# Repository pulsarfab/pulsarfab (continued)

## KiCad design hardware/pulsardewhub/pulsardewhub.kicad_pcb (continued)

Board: 4 copper layers, 233 parts (0 on the bottom side), 133 nets, no tracks yet.

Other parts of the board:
FID1, FID2, FID3: Fiducial; Fiducial_1mm_Mask2mm
H1, H2, H3, H4: M3; MountingHole_3.2mm_M3

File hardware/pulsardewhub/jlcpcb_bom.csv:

"Item","Designator","Comment","Footprint","Qty","LCSC Part #","MPN","Manufacturer"
"1","C1,C3,C4,C23,C33,C50,C52,C70,C71,C501,C503,C601,C603,C701,C703,C801,C803,C903-C909,C914,C915","100n","Capacitor_SMD:C_0603_1608Metric","26","C14663","CC0603KRX7R9BB104","YAGEO"
"2","C2","4.7u / 16V","Capacitor_SMD:C_0603_1608Metric","1","C19666","CL10A475KO8NNNC","Samsung Electro-Mechanics"
"3","C10,C22,C51,C910-C913","1u / 50V","Capacitor_SMD:C_0603_1608Metric","7","C15849","CL10A105KB8NNNC","Samsung Electro-Mechanics"
"4","C11,C13,C31,C101,C102,C201,C202,C301,C302,C401,C402","100n / 50V","Capacitor_SMD:C_0603_1608Metric","11","C14663","CC0603KRX7R9BB104","YAGEO"
"5","C12","470u / 35V","Capacitor_THT:CP_Radial_D10.0mm_P5.00mm","1","C106703","ERS1VM471G16OT","AISHI"
"6","C20,C30","10u / 50V","Capacitor_SMD:C_1210_3225Metric","2","C138687","CL32B106KBJNNNE","Samsung Electro-Mechanics"
"7","C21","220n / 50V","Capacitor_SMD:C_0603_1608Metric","1","C64705","CL10B224KB8NNNC","Samsung Electro-Mechanics"
"8","C24-C27,C34-C37","22u / 25V","Capacitor_SMD:C_1206_3216Metric","8","C12891","CL31A226KAHNNNE","Samsung Electro-Mechanics"
"9","C103,C203,C303,C403","4.7n / 50V","Capacitor_SMD:C_0603_1608Metric","4","C1621","CL10B472KB8NNNC","Samsung Electro-Mechanics"
"10","C104,C204,C304,C404","10n","Capacitor_SMD:C_0603_1608Metric","4","C1589","CL10B103KB8NNNC","Samsung Electro-Mechanics"
"11","C502,C602,C702,C802","150u / 10V / 20%","pulsarfab:CP_RVT_D6.3mm_L5.4mm","4","C970688","RVT1A151M0605 150UF 10V","DMBJ"
"12","C901,C902","18p / C0G","Capacitor_SMD:C_0603_1608Metric","2","C342890","CGA3E2C0G1H180JT0Y0N","TDK"
"13","D10","SMCJ18A","Diode_SMD:D_SMC","1","C438102","SMCJ18A","Jingdao Microelectronics"
"14","D51,D61","SMBJ20A","Diode_SMD:D_SMB","2","C364296","SMBJ20A","MDD(Microdiode Semiconductor)"
"15","D101,D201,D301,D401","SS54","Diode_SMD:D_SMA","4","C22452","SS54","MDD(Microdiode Semiconductor)"
"16","F10","30A / upstream budget","pulsarfab:Fuse_S1032_10.3x3.2mm","1","C553917","S1032-F-30.0A","SART"
"17","F51,F61","7A heater fuse","Fuse:Fuse_Littelfuse-NANO2-451_453","2","C99548","0451007.MRL","Littelfuse"
"18","J1","SWD","Connector_PinHeader_2.54mm:PinHeader_1x05_P2.54mm_Vertical","1","C492404","PZ254V-11-05P","XFCN"
"19","J10","XT60: 2=PLUS, 1=GND","pulsarfab:AMASS_XT60PW-M_Edge","1","C98732","XT60PW-M","Changzhou Amass Elec"
"20","J40","USB-C upstream","pulsarfab:USB_C_HRO_TYPE-C-31-M-12","1","C165948","TYPE-C-31-M-12","Korean Hroparts Elec"
"21","J51","HEATER 1","pulsarfab:TerminalBlock_KEFA_KF128_2P_P5.08mm","1","C474952","KF128-5.08-2P-AA","Cixi Kefa Elec"
"22","J61","HEATER 2","pulsarfab:TerminalBlock_KEFA_KF128_2P_P5.08mm","1","C474952","KF128-5.08-2P-AA","Cixi Kefa Elec"
"23","J101,J201,J301,J401","5A DC / center +","pulsarfab:BarrelJack_XKB_DC-005K-5A_Edge","4","C2880546","DC-005K-5A-2.0","XKB Connection"
"24","J501,J601,J701,J801","USB-A / 500mA","pulsarfab:USB_A_SHOUHAN_AF90ZJWG_THT","4","C456019","AF 90 ZJWG","SHOU HAN"
"25","L20","8.2u / 10A sat","pulsarfab:L_SXN_SMMS1050","1","C149543","SMMS1050-8R2M","Shun Xiang Nuo"
"26","L30","6.8u / 12A sat","pulsarfab:L_SXN_SMMS1050","1","C149542","SMMS1050-6R8M","Shun Xiang Nuo"
"27","Q10,Q11","SiR680LDP","Package_SO:PowerPAK_SO-8_Single","2","C3279524","SIR680LDP-T1-RE3","Vishay"
"28","Q51,Q61","AOD4184A","Package_TO_SOT_SMD:TO-252-2","2","C5370959","AOD4184A","TECH PUBLIC"
"29","R1,R2","4.7k","Resistor_SMD:R_0603_1608Metric","2","C23162","0603WAF4701T5E","UNI-ROYAL"
"30","R20,R30,R53,R63,R101,R201,R301,R401,R502,R602,R702,R802,R923,R924","100k","Resistor_SMD:R_0603_1608Metric","14","C25803","0603WAF1003T5E","UNI-ROYAL"
"31","R21","24.9k","Resistor_SMD:R_0603_1608Metric","1","C25962","0603WAF2492T5E","UNI-ROYAL"
"32","R31,R102,R202,R302,R402","20k","Resistor_SMD:R_0603_1608Metric","5","C4184","0603WAF2002T5E","UNI-ROYAL"
"33","R32","12k","Resistor_SMD:R_0603_1608Metric","1","C22790","0603WAF1202T5E","UNI-ROYAL"
"34","R50","2m / 3W / 1%","Resistor_SMD:R_2512_6332Metric","1","C2994640","HoLLR2512-3W-2mR-1%","Milliohm"
"35","R51,R61,R71,R73-R78,R104-R106,R109,R204-R206,R209,R304-R306,R309,R404-R406,R409,R901-R918,R920,R925-R928","10k","Resistor_SMD:R_0603_1608Metric","48","C25804","0603WAF1002T5E","UNI-ROYAL"
"36","R52,R62","47","Resistor_SMD:R_0603_1608Metric","2","C23182","0603WAF470JT5E","UNI-ROYAL"
"37","R70","220k","Resistor_SMD:R_0603_1608Metric","1","C22961","0603WAF2203T5E","UNI-ROYAL"
"38","R72","470k","Resistor_SMD:R_0603_1608Metric","1","C23178","0603WAF4703T5E","UNI-ROYAL"
"39","R103,R203,R303,R403","150k","Resistor_SMD:R_0603_1608Metric","4","C22807","0603WAF1503T5E","UNI-ROYAL"
"40","R107,R207,R307,R407","1k / 1%","Resistor_SMD:R_0603_1608Metric","4","C21190","0603WAF1001T5E","UNI-ROYAL"
"41","R110,R210,R310,R410","1k","Resistor_SMD:R_0603_1608Metric","4","C21190","0603WAF1001T5E","UNI-ROYAL"
"42","R501,R601,R701,R801","43.2k / 1%","Resistor_SMD:R_0603_1608Metric","4","C23053","0603WAF4322T5E","UNI-ROYAL"
"43","R919","12k / 1%","Resistor_SMD:R_0603_1608Metric","1","C22790","0603WAF1202T5E","UNI-ROYAL"
"44","R921,R922","5.1k","Resistor_SMD:R_0603_1608Metric","2","C23186","0603WAF5101T5E","UNI-ROYAL"
"45","U1","STM32G0B1KBU6","Package_DFN_QFN:UFQFPN-32-1EP_5x5mm_P0.5mm_EP3.5x3.5mm","1","C5159549","STM32G0B1KBU6","ST"
"46","U2","SHT40-AD1B-R2","Sensor_Humidity:Sensirion_DFN-4_1.5x1.5mm_P0.8mm_SHT4x_NoCentralPad","1","C2909890","SHT40-AD1B-R2","Sensirion"
"47","U10","LM74700QDBV","Package_TO_SOT_SMD:SOT-23-6","1","C2941042","LM74700QDBVRQ1","TI"
"48","U20","LMR33630ADDA","Package_SO:Texas_HSOP-8-1EP_3.9x4.9mm_P1.27mm","1","C841384","LMR33630ADDAR","TI"
"49","U30","LMR51610XDBVR","Package_TO_SOT_SMD:SOT-23-6","1","C20539658","LMR51610XDBVR","Texas Instruments"
"50","U40","USB2517-JZX","Package_DFN_QFN:QFN-64-1EP_9x9mm_P0.5mm_EP4.7x4.7mm","1","C1521556","USB2517-JZX","MICROCHIP"
"51","U41","TPS3808G33DBV","Package_TO_SOT_SMD:SOT-23-6","1","C43698","TPS3808G33DBVR","TI"
"52","U42,U502,U602,U702,U802","USBLC6-2SC6","Package_TO_SOT_SMD:SOT-23-6","5","C7519","USBLC6-2SC6","ST"
"53","U50","TC4427AVOA713","Package_SO:SOIC-8_3.9x4.9mm_P1.27mm","1","C624944","TC4427AVOA713","MICROCHIP"
"54","U51","INA226","Package_SO:TSSOP-10_3x3mm_P0.5mm","1","C49851","INA226AIDGSR","Texas Instruments"
"55","U70","TPS3700DDC","Package_TO_SOT_SMD:SOT-23-6","1","C33002","TPS3700DDCR","TI"
"56","U71","SN74LVC08APW","Package_SO:TSSOP-14_4.4x5mm_P0.65mm","1","C465737","SN74LVC08APWR","Texas Instruments"
"57","U101,U201,U301,U401","TPS25974LRPW","pulsarfab:TI_RPW0010A_VQFN10_2x2mm","4","C3662931","TPS25974LRPWR","Texas Instruments"
"58","U102,U202,U302,U402","TVS1800DRV","Package_SON:WSON-6-1EP_2x2mm_P0.65mm_EP1x1.6mm","4","C2649846","TVS1800DRVR","Texas Instruments"
"59","U501,U601,U701,U801","TPS2553DBV","Package_TO_SOT_SMD:SOT-23-6","4","C55266","TPS2553DBVR","TI"
"60","Y40","24MHz / CL=12pF","Crystal:Crystal_SMD_3225-4Pin_3.2x2.5mm","1","C5181479","3225 24M 12PF 10PPM","SOSET"

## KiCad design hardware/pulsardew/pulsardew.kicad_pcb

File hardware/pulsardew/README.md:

# PulsarDew schematic

PulsarDew is the original four-channel dew heater controller. For the expanded
product with switched DC power outlets, two heaters and a USB hub, see
**[PulsarPower](../pulsardewhub/README.md)** (formerly PulsarDew Hub).

Open `pulsardew.kicad_pro` in KiCad 10, then open its root schematic. Revision
0.2 is a connected nine-page hierarchy: system wiring, controller, current
monitor, logic supply, SHT40, and four instances of the heater driver.
Edit the `.kicad_sch` files directly in KiCad; they are the authoritative design.

## Electrical connections

The root drawing shows the protected DC supply through the 2 mΩ shunt to all
four heaters. The logic regulator branches off before the shunt. The INA226
therefore measures **combined heater current**, including gate-drive current,
not four independent currents. Its address is 0x40; the SHT40 address is 0x44.

| Signal | MCU pin | Connection |
| --- | --- | --- |
| Heater 0–3 PWM | PA0–PA3, pads 7–10 | Four independent driver inputs; active low |
| I2C SCL / SDA | PB6 / PB7, pads 30 / 31 | INA226 and SHT40, one pair of 4.7 kΩ pull-ups |
| USB D− / D+ | PA11 / PA12, pads 22 / 23 | Both corresponding USB-C pin pairs |
| USB VBUS sense | PA9, pad 19 | 100 kΩ / 100 kΩ divider |
| SWDIO / SWCLK | PA13 / PA14, pads 24 / 25 | J4 pins 2 / 3 |
| Reset | PF2/NRST, pad 6 | 100 nF to ground and J4 pin 4 |

J4 pins 1 and 5 provide target voltage reference and ground. J101, J201, J301,
and J401 are heater connectors: pin 1 is measured VIN; pin 2 is a switched
return and must not be connected directly to ground. J2 and J3 are parallel
power-input options; use one supply source.

USB is self-powered from the DC supply. USB VBUS is only sensed and is isolated
from the DC and 3.3 V rails. Firmware must disable the MCU's UCPD dead-battery
pull-down on PA9 before sensing VBUS and must enable USB attachment only while
VBUS is present. Firmware implementation is outside this schematic change.

## Repairs made in revision 0.2

- Restored qualified symbol caches and per-sheet instance references. The
  previous files loaded as missing symbols and exported no components.
- Rewired the hierarchy and component pins, with visible branches and junctions.
- Corrected the 2N7002 to gate/source/drain pads 1/2/3. The AOD4184A uses
  gate/drain/source pads 1/2/3.
- Corrected I2C to PB6/PB7; completed both USB-C orientations, reset, bypass
  capacitors, debug access, power input and heater outputs.
- Replaced the incorrectly substituted L78L33 symbol and 12 V HT7333-A part
  with a dedicated **HT7333-1** symbol: pad 1 GND, pad 2 VIN/tab, pad 3 VOUT.
  This retains the stated 12–20 V input range. Input/output bypassing is
  10 µF plus 100 nF as shown in the manufacturer's application circuit.
- Corrected resistor footprint assignments and the missing terminal-block
  library reference. New or changed components without confirmed sourcing
  have no invented LCSC number.

## Reproducible verification

From `hardware/`:

```sh
make check-pulsardew
make verify-pulsardew
make render-pulsardew
```

`verify-pulsardew` runs KiCad ERC with all severities, including exclusions,
then checks exact pin membership of all 32 connected nets and all 21 intentional
no-connects. It requires 58 uniquely referenced components and checks that
every schematic pin has a pad in its assigned footprint. This catches shorts
between rails/channels, incorrect semiconductor pin mapping, missing USB pin
pairs and bypassed shunt connections, even where ERC alone would permit them.

Verified with KiCad CLI 10.0.6: **zero ERC errors, warnings or exclusions**.
The six distinct page designs were also rendered and visually reviewed; four
heater instances share the same drawing with separate reference numbers/nets.

## PCB floorplan (revision 0.3)

The PCB now contains the 58 schematic footprints plus four board-only M3
mounting holes, within a provisional **100 × 80 mm** outline. Mount centers are
4 mm from each edge (92 × 72 mm spacing). It opens in KiCad's PCB Editor with
the schematic UUID links and all 54 named nets preserved.

The left edge carries the alternative DC inputs. Input diode, bulk capacitor,
shunt and INA226 sit together, with space for Kelvin traces from the shunt.
Four identical heater stages and their outward-facing terminals occupy the
bottom edge. The USB connector and MCU are at the top, with MCU bypassing
adjacent to its supply pins. SHT40 is at the upper-right edge, away from the
power stages; a rule area prevents routing/pours below its sensing package.
The MCU uses KiCad's ST UFQFPN-32 footprint, including segmented paste openings,
instead of the inherited footprint whose silkscreen crossed all perimeter pads.

`make verify-floorplan-pulsardew` checks placement and schematic parity. KiCad
10.0.6 reports **zero courtyard overlaps, zero schematic parity issues,
and 131 unconnected items**. The HRO USB-C replacement resolves the former
locator-hole clearance violations; the strict placement check now passes with
zero DRC violations and no exclusions. It is deliberately a floorplan: no
tracks or copper pours are routed.
Power, USB and sense net classes provide routing starting points; their widths
are not a current or controlled-impedance certification. Use an uninterrupted
ground reference under USB, keep heater returns out of the logic/sensor return
path, and derive final widths/USB geometry from the selected fabrication stackup.

## Before manufacture

Connectivity verification does not
validate land-pattern geometry, current capacity, thermal behavior, protection
or assembly sourcing. USB-C J1 now sources HRO TYPE-C-31-M-12 (C165948), using its own
project footprint; see the [connector review](../pulsardewhub/docs/usb-c-sourcing.md). Barrel J2
now sources owned XKB DC-005K-5A-2.0 (C2880546) with its own slot pattern; pins 2 and 3 are both grounded.
See the [XKB drawing/sample qualification note](../pulsardewhub/README.md#stocked-barrel-sockets-and-retained-sensor).
Remaining supplier codes must be reconciled with the exact packages before ordering; the HT7333-1 orderable variant and
capacitor effective values at bias need BOM confirmation.

The inherited inverter driver defaults off only while 3.3 V is present. Loss
or delayed startup of logic power can turn a heater on. Add an independent
hardware inhibit if fail-off behavior under that condition is required. Use
slow heater PWM and validate MOSFET switching losses with this 10 kΩ pull-up
driver. Verify the input diode, connector, shunt and trace current limits;
the INA226 measurement range is not a board current rating. Check LDO
dissipation at the worst input voltage and load. USB ESD protection and input
overcurrent/transient protection remain hardware design review items.

## Pinout and circuit references

- [ST STM32G0B1 datasheet, UFQFPN32 and alternate-function tables](https://www.st.com/resource/en/datasheet/stm32g0b1me.pdf)
- [TI INA226 datasheet](https://www.ti.com/lit/ds/symlink/ina226.pdf)
- [Sensirion SHT4x datasheet](https://sensirion.com/media/documents/33FD6951/662A593A/HT_DS_Datasheet_SHT4x.pdf)
- [Holtek HT73xx-1, pin assignment and application circuit](https://www.holtek.com/webapi/116711/HT73xx-1v120.pdf)
- [Holtek HT73xx, original part's 12 V operating limit](https://www.holtek.com/webapi/116711/HT73xxv180.pdf)
- [onsemi NDS7002A / 2N7002 pinout](https://www.onsemi.com/pdf/datasheet/nds7002a-d.pdf)
- [AOS AOD4184A datasheet](https://www.aosmd.com/res/data_sheets/AOD4184A.pdf)

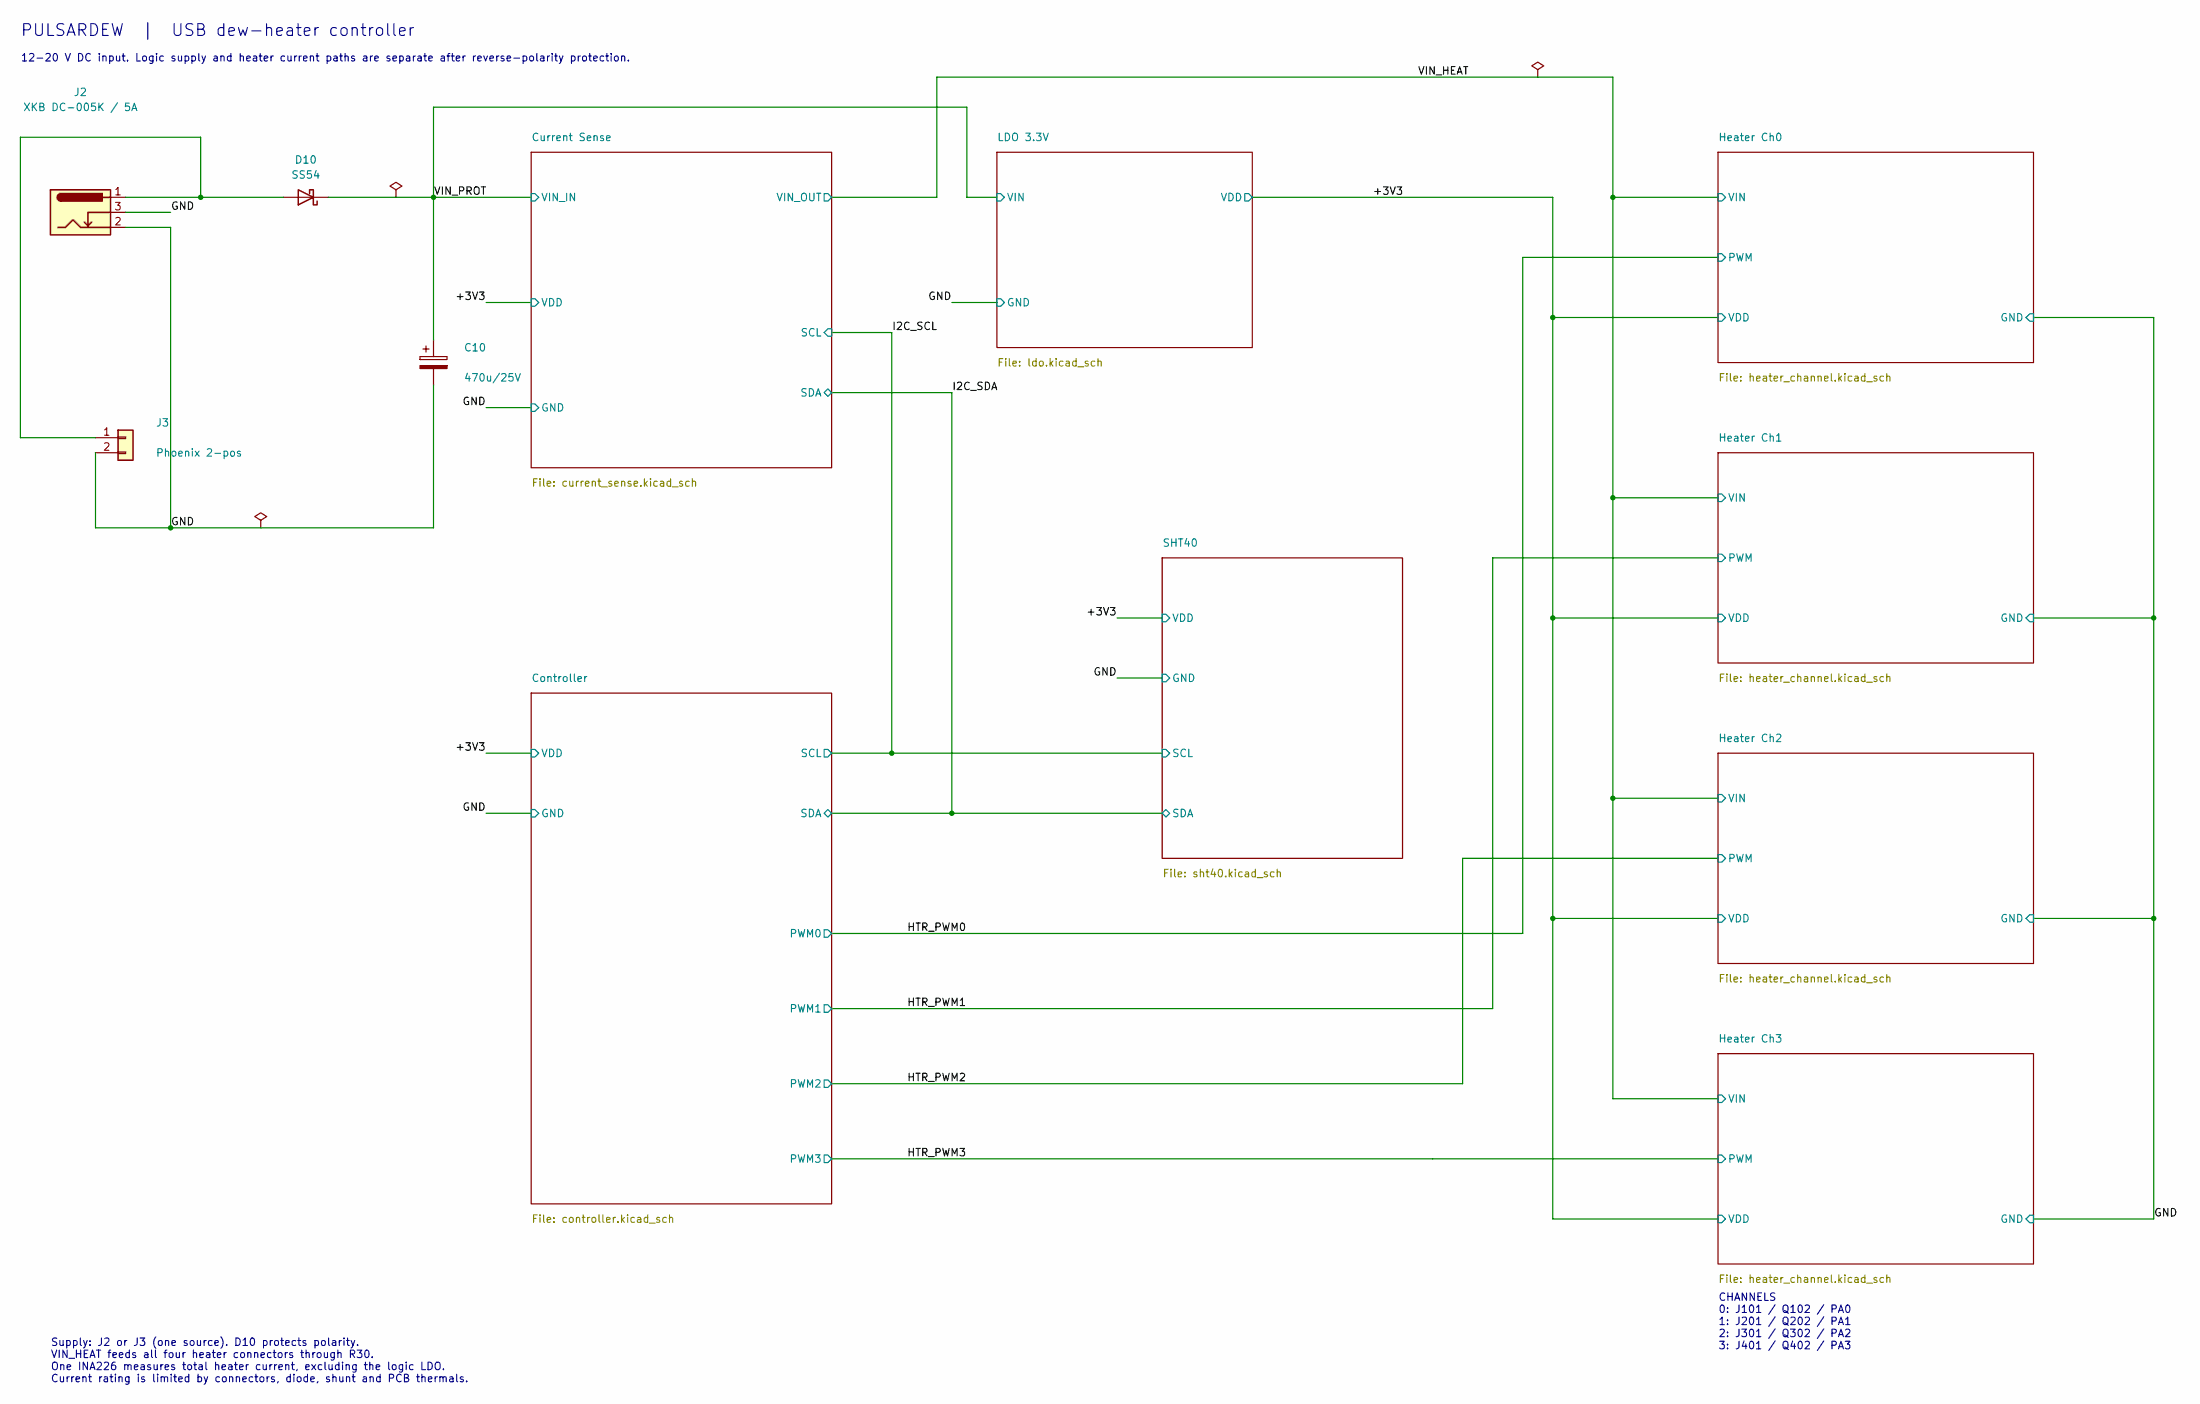
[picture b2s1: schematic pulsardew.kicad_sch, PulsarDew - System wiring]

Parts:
C10: 470u/25V; CP_Elec_8x10.5
D10: SS54; D_SMA_Handsoldering; MPN SS54; LCSC C22452
J2: XKB DC-005K / 5A; BarrelJack_XKB_DC-005K-5A_Edge; MPN DC-005K-5A-2.0; LCSC C2880546
J3: Phoenix 2-pos; TerminalBlock_Phoenix_MKDS-1,5-2-5.08_1x02_P5.08mm_Horizont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

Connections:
/GND: C10.2, J2.2, J2.3, J3.2; also elsewhere on the board
/VIN_PROT: C10.1, D10.1 (K); also elsewhere on the board
unnamed: D10.2 (A), J2.1, J3.1

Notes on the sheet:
PULSARDEW | USB dew-heater controller
12-20 V DC input. Logic supply and heater current paths are separate after reverse-polarity protection.
Supply: J2 or J3 (one source). D10 protects polarity. VIN_HEAT feeds all four heater connectors through R30. One INA226 measures total heater current, excluding the logic LDO. Current rating is limited by connectors, diode, shunt and PCB thermals.
CHANNELS 0: J101 / Q102 / PA0 1: J201 / Q202 / PA1 2: J301 / Q302 / PA2 3: J401 / Q402 / PA3

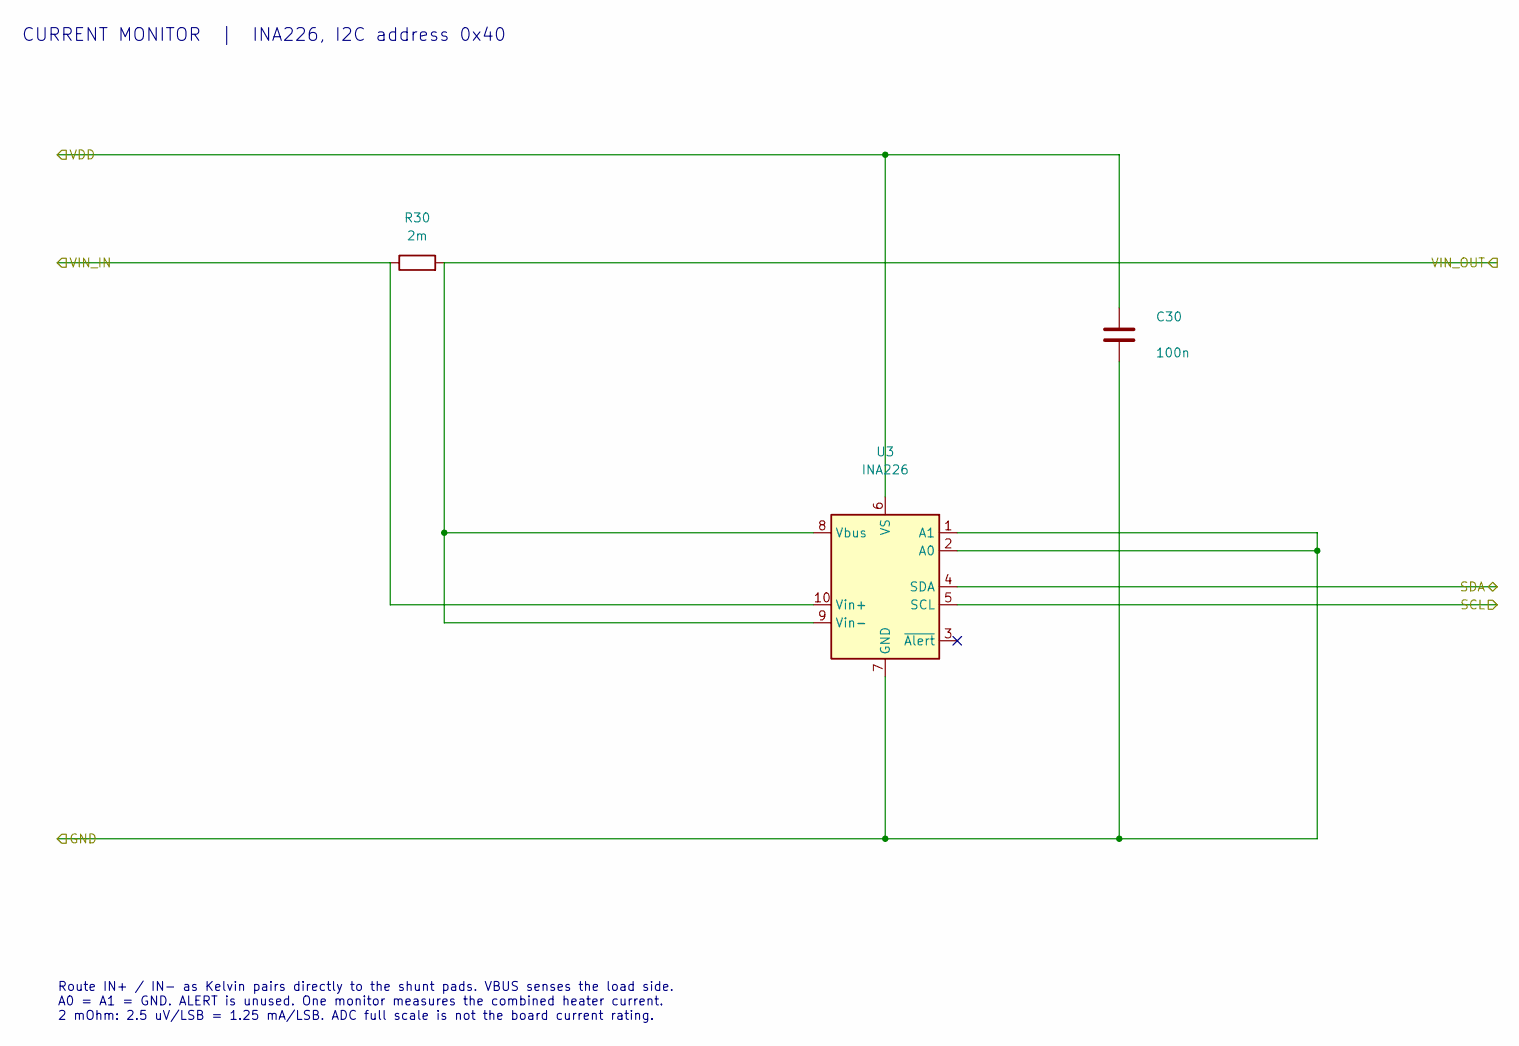
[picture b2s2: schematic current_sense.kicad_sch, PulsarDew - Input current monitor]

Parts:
C30: 100n; C_0402_1005Metric
R30: 2m; R_2512_6332Metric; MPN RLP25FEGR002; LCSC C459679
U3: INA226; TSSOP-10_3x3mm_P0.5mm; MPN INA226AIDGSR; LCSC C49851

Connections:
/+3V3: C30.1, U3.6 (VS); also elsewhere on the board
/GND: C30.2, U3.1 (A1), U3.2 (A0), U3.7 (GND); also elsewhere on the board
/I2C_SCL: U3.5 (SCL); also elsewhere on the board
/I2C_SDA: U3.4 (SDA); also elsewhere on the board
/VIN_HEAT: R30.2, U3.8 (Vbus), U3.9 (Vin-); also elsewhere on the board
/VIN_PROT: R30.1, U3.10 (Vin+); also elsewhere on the board

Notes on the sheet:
CURRENT MONITOR | INA226, I2C address 0x40
Route IN+ / IN- as Kelvin pairs directly to the shunt pads. VBUS senses the load side. A0 = A1 = GND. ALERT is unused. One monitor measures the combined heater current. 2 mOhm: 2.5 uV/LSB = 1.25 mA/LSB. ADC full scale is not the board current rating.

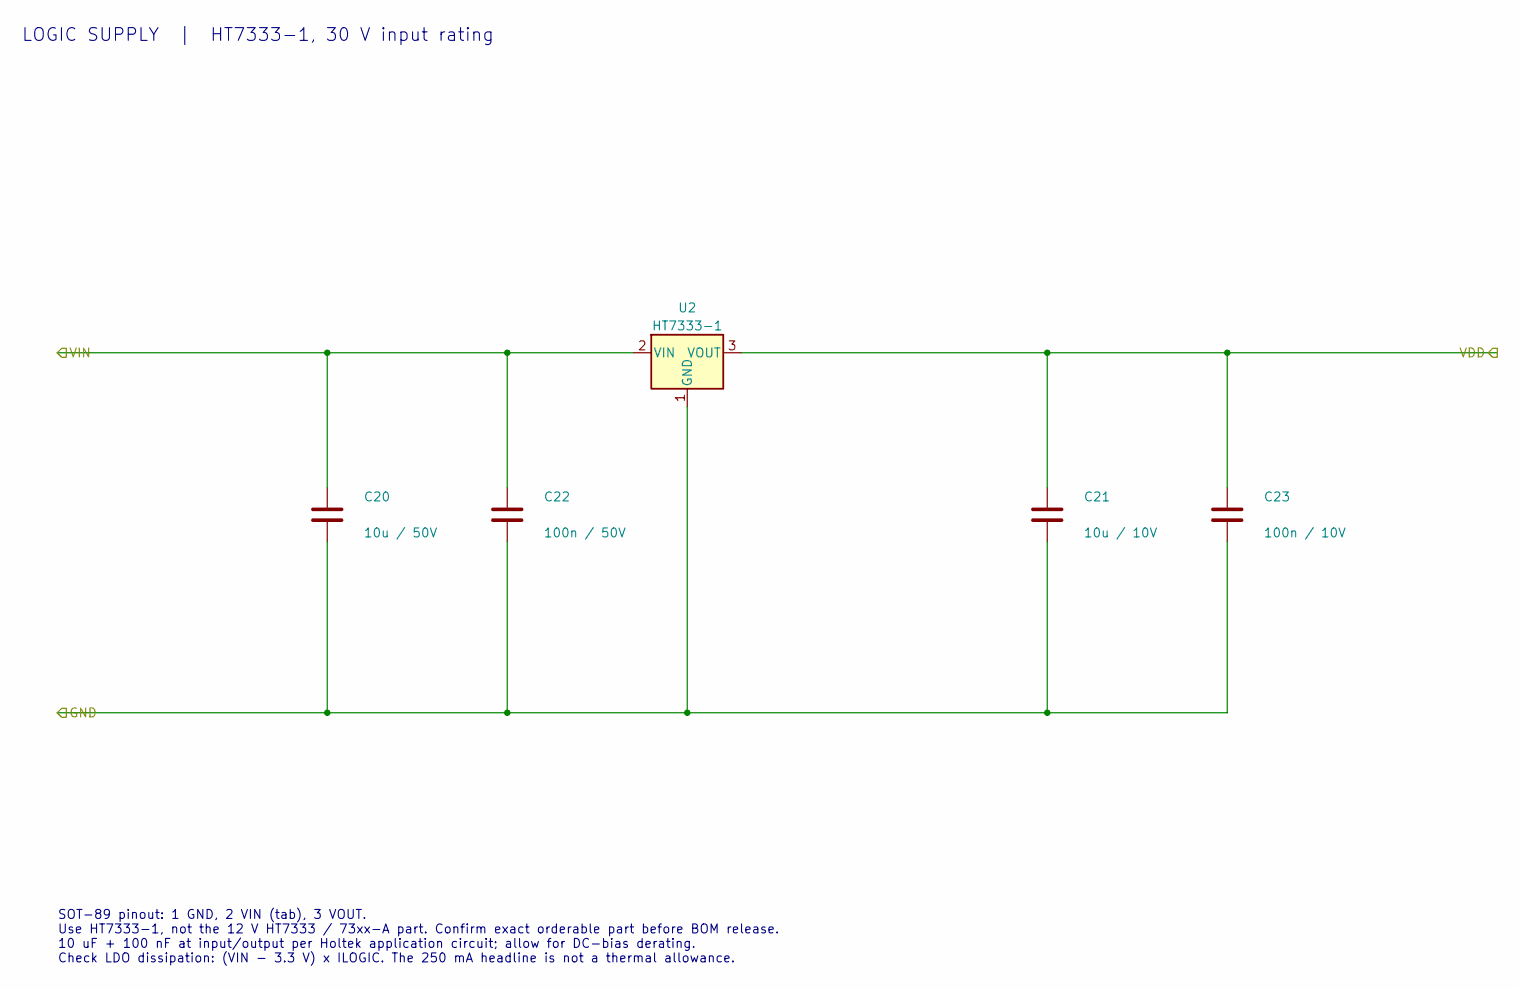
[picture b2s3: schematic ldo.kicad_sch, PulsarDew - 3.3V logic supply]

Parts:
C20: 10u / 50V; C_1210_3225Metric
C21: 10u / 10V; C_0805_2012Metric
C22: 100n / 50V; C_0603_1608Metric
C23: 100n / 10V; C_0402_1005Metric
U2: HT7333-1; SOT-89-3; MPN HT7333-1

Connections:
/+3V3: C21.1, C23.1, U2.3 (VOUT); also elsewhere on the board
/GND: C20.2, C21.2, C22.2, C23.2, U2.1 (GND); also elsewhere on the board
/VIN_PROT: C20.1, C22.1, U2.2 (VIN); also elsewhere on the board

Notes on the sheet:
LOGIC SUPPLY | HT7333-1, 30 V input rating
SOT-89 pinout: 1 GND, 2 VIN (tab), 3 VOUT. Use HT7333-1, not the 12 V HT7333 / 73xx-A part. Confirm exact orderable part before BOM release. 10 uF + 100 nF at input/output per Holtek application circuit; allow for DC-bias derating. Check LDO dissipation: (VIN - 3.3 V) x ILOGIC. The 250 mA headline 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

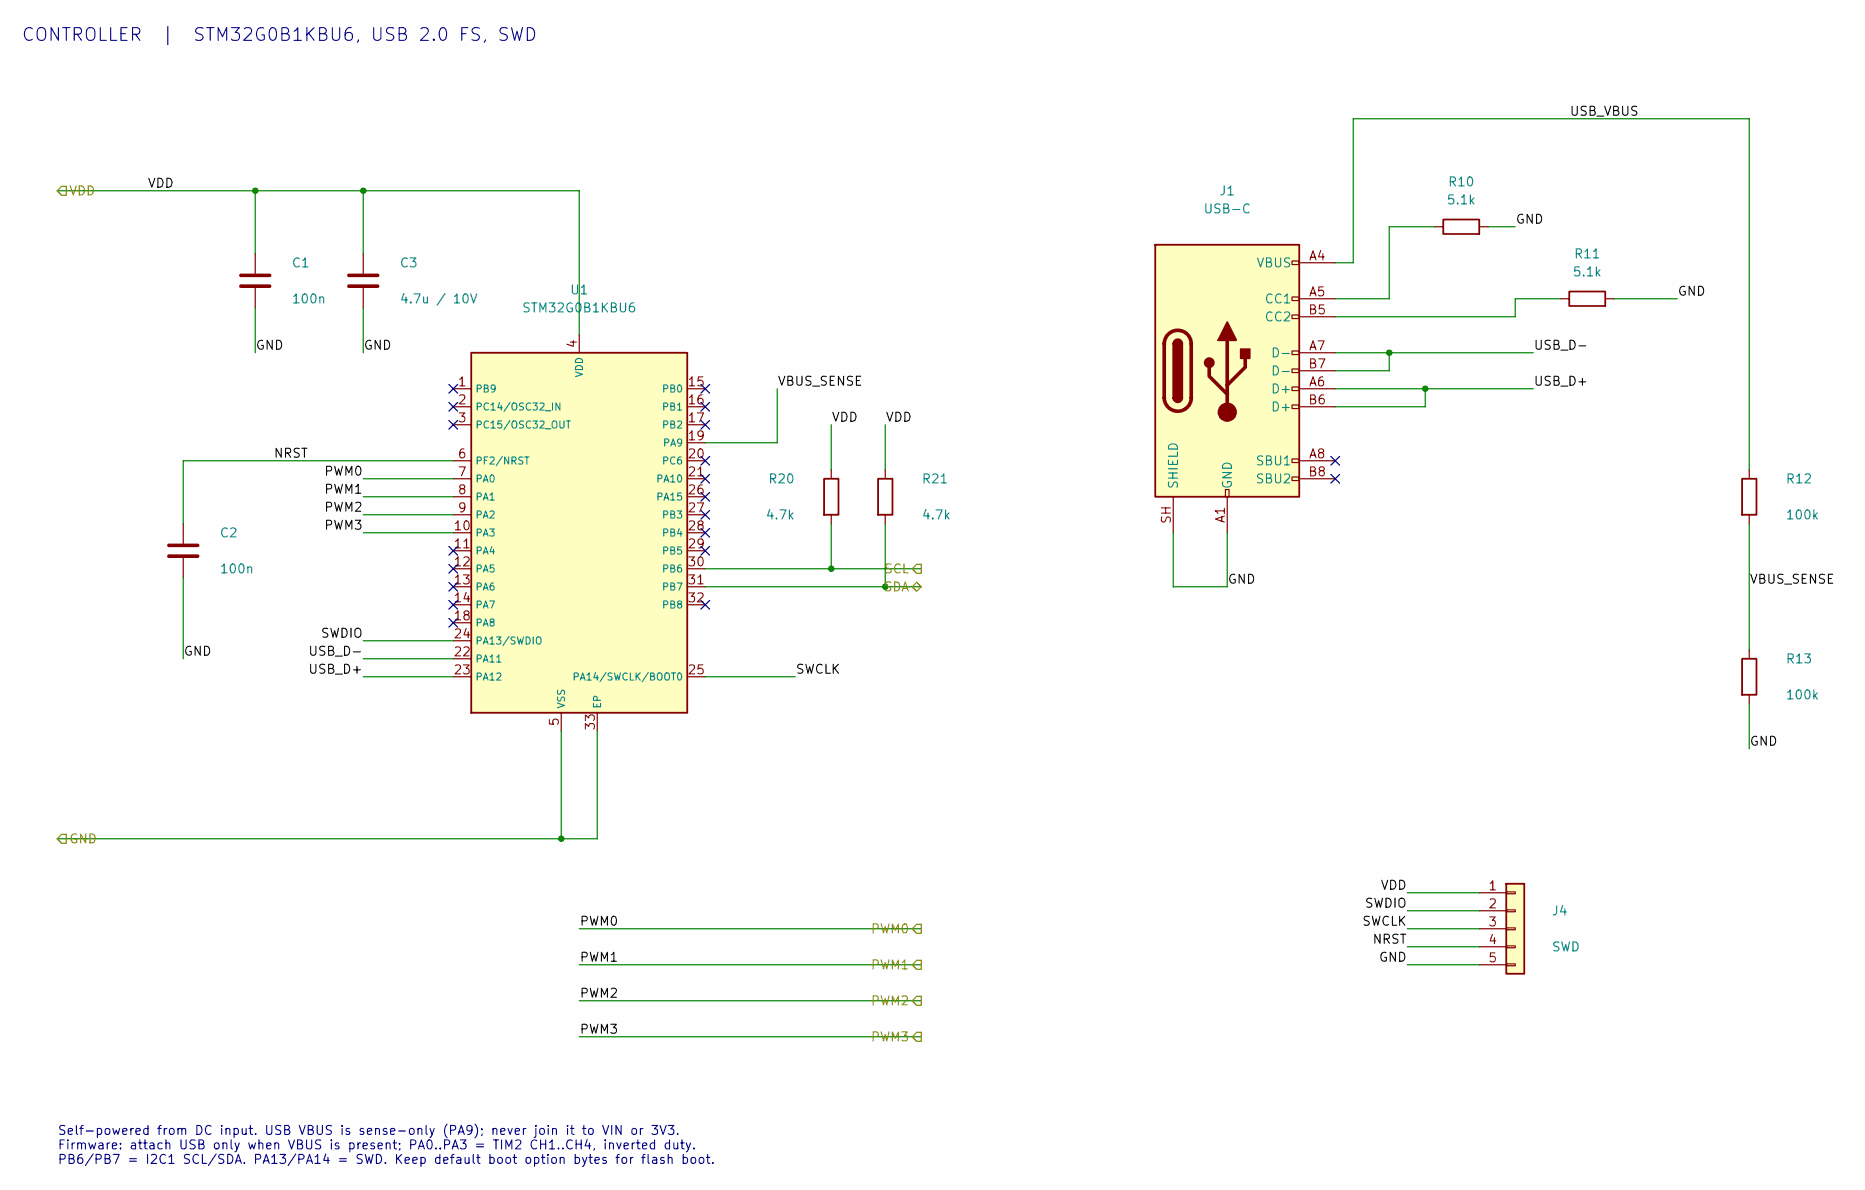
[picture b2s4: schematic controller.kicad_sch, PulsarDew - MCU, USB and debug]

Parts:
C1, C2: 100n; C_0402_1005Metric
C3: 4.7u / 10V; C_0402_1005Metric
J1: USB-C; USB_C_HRO_TYPE-C-31-M-12; MPN TYPE-C-31-M-12; LCSC C165948
J4: SWD; PinHeader_1x05_P2.54mm_Vertical
R10, R11: 5.1k; R_0402_1005Metric
R12, R13: 100k; R_0402_1005Metric
R20, R21: 4.7k; R_0402_1005Metric
U1: STM32G0B1KBU6; UFQFPN-32-1EP_5x5mm_P0.5mm_EP3.5x3.5mm; MPN STM32G0B1KBU6; LCSC C5159549

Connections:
/+3V3: C1.1, C3.1, J4.1, R20.1, R21.1, U1.4 (VDD); also elsewhere on the board
/Controller/NRST: C2.1, J4.4, U1.6 (PF2/NRST)
/Controller/SWCLK: J4.3, U1.25 (PA14/SWCLK/BOOT0)
/Controller/SWDIO: J4.2, U1.24 (PA13/SWDIO)
/Controller/USB_D+: J1.A6 (D+), J1.B6 (D+), U1.23 (PA12)
/Controller/USB_D-: J1.A7 (D-), J1.B7 (D-), U1.22 (PA11)
/Controller/USB_VBUS: J1.A4 (VBUS), J1.A9 (VBUS), J1.B4 (VBUS), J1.B9 (VBUS), R12.1
/Controller/VBUS_SENSE: R12.2, R13.1, U1.19 (PA9)
/GND: C1.2, C2.2, C3.2, J1.A1 (GND), J1.A12 (GND), J1.B1 (GND), J1.B12 (GND), J1.SH (SHIELD), J4.5, R10.2, R11.2, R13.2, U1.5 (VSS), U1.33 (EP); also elsewhere on the board
/HTR_PWM0: U1.7 (PA0); also elsewhere on the board
/HTR_PWM1: U1.8 (PA1); also elsewhere on the board
/HTR_PWM2: U1.9 (PA2); also elsewhere on the board
/HTR_PWM3: U1.10 (PA3); also elsewhere on the board
/I2C_SCL: R20.2, U1.30 (PB6); also elsewhere on the board
/I2C_SDA: R21.2, U1.31 (PB7); also elsewhere on the board
unnamed: J1.A5 (CC1), R10.1
unnamed: J1.B5 (CC2), R11.1

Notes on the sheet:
CONTROLLER | STM32G0B1KBU6, USB 2.0 FS, SWD
Self-powered from DC input. USB VBUS is sense-only (PA9); never join it to VIN or 3V3. Firmware: attach USB only when VBUS is present; PA0..PA3 = TIM2 CH1..CH4, inverted duty. PB6/PB7 = I2C1 SCL/SDA. PA13/PA14 = SWD. Keep default boot option bytes for flash boot.

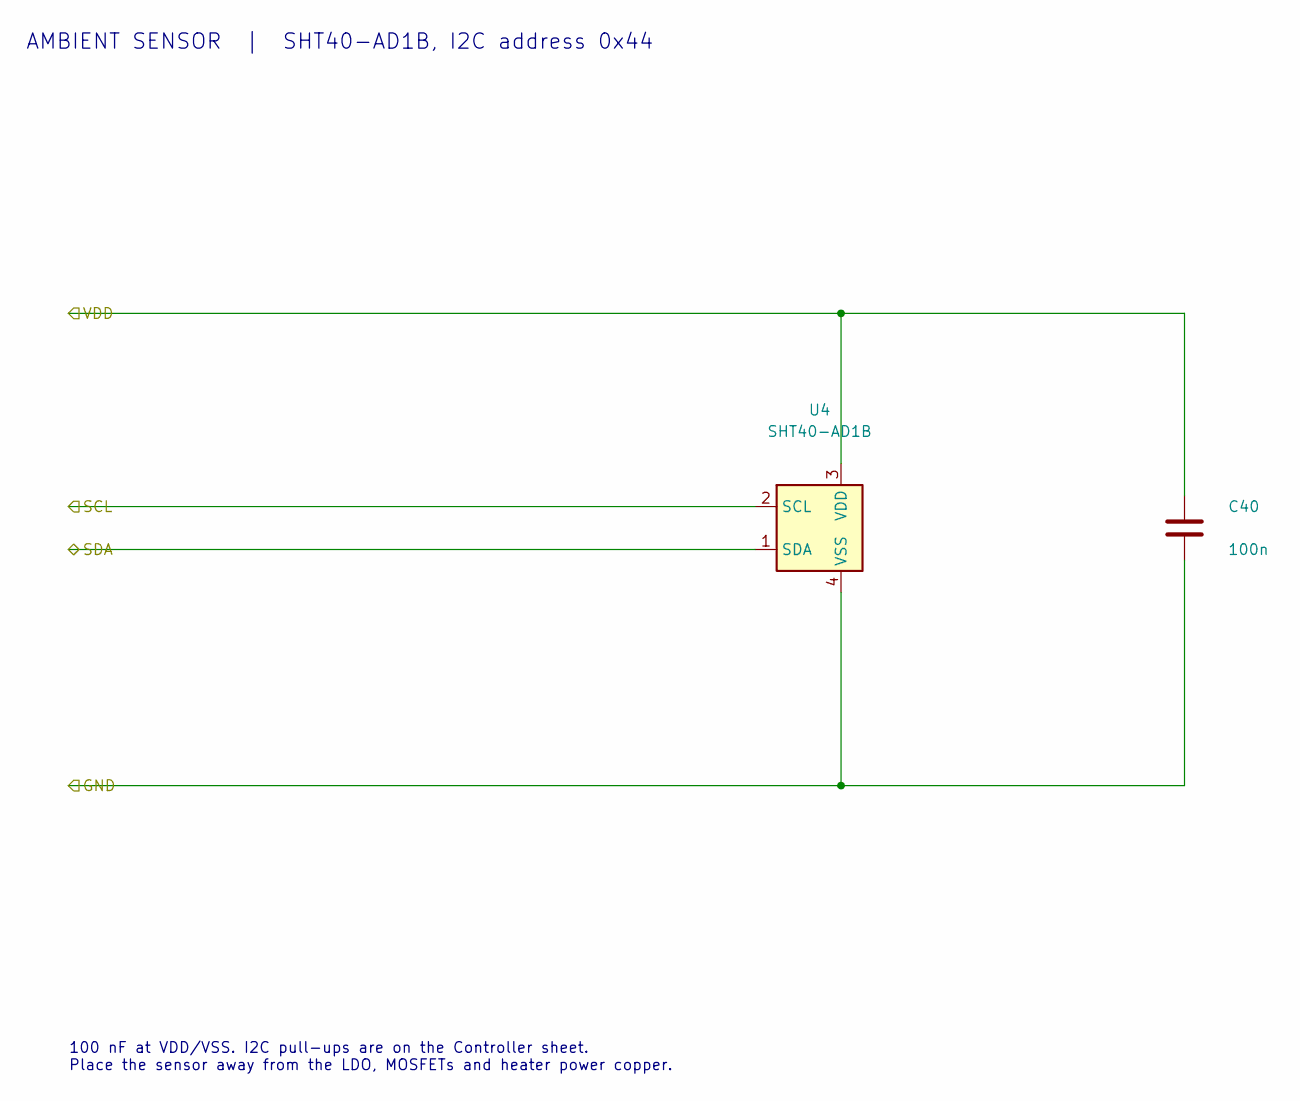
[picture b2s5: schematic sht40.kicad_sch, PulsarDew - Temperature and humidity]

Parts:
C40: 100n; C_0402_1005Metric
U4: SHT40-AD1B; Sensirion_DFN-4_1.5x1.5mm_P0.8mm_SHT4x_NoCentralPad; MPN SHT40-AD1B-R2; LCSC C2909890

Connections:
/+3V3: C40.1, U4.3 (VDD); also elsewhere on the board
/GND: C40.2, U4.4 (VSS); also elsewhere on the board
/I2C_SCL: U4.2 (SCL); also elsewhere on the board
/I2C_SDA: U4.1 (SDA); also elsewhere on the board

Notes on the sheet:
AMBIENT SENSOR | SHT40-AD1B, I2C address 0x44
100 nF at VDD/VSS. I2C pull-ups are on the Controller sheet. Place the sensor away from the LDO, MOSFETs and heater power copper.

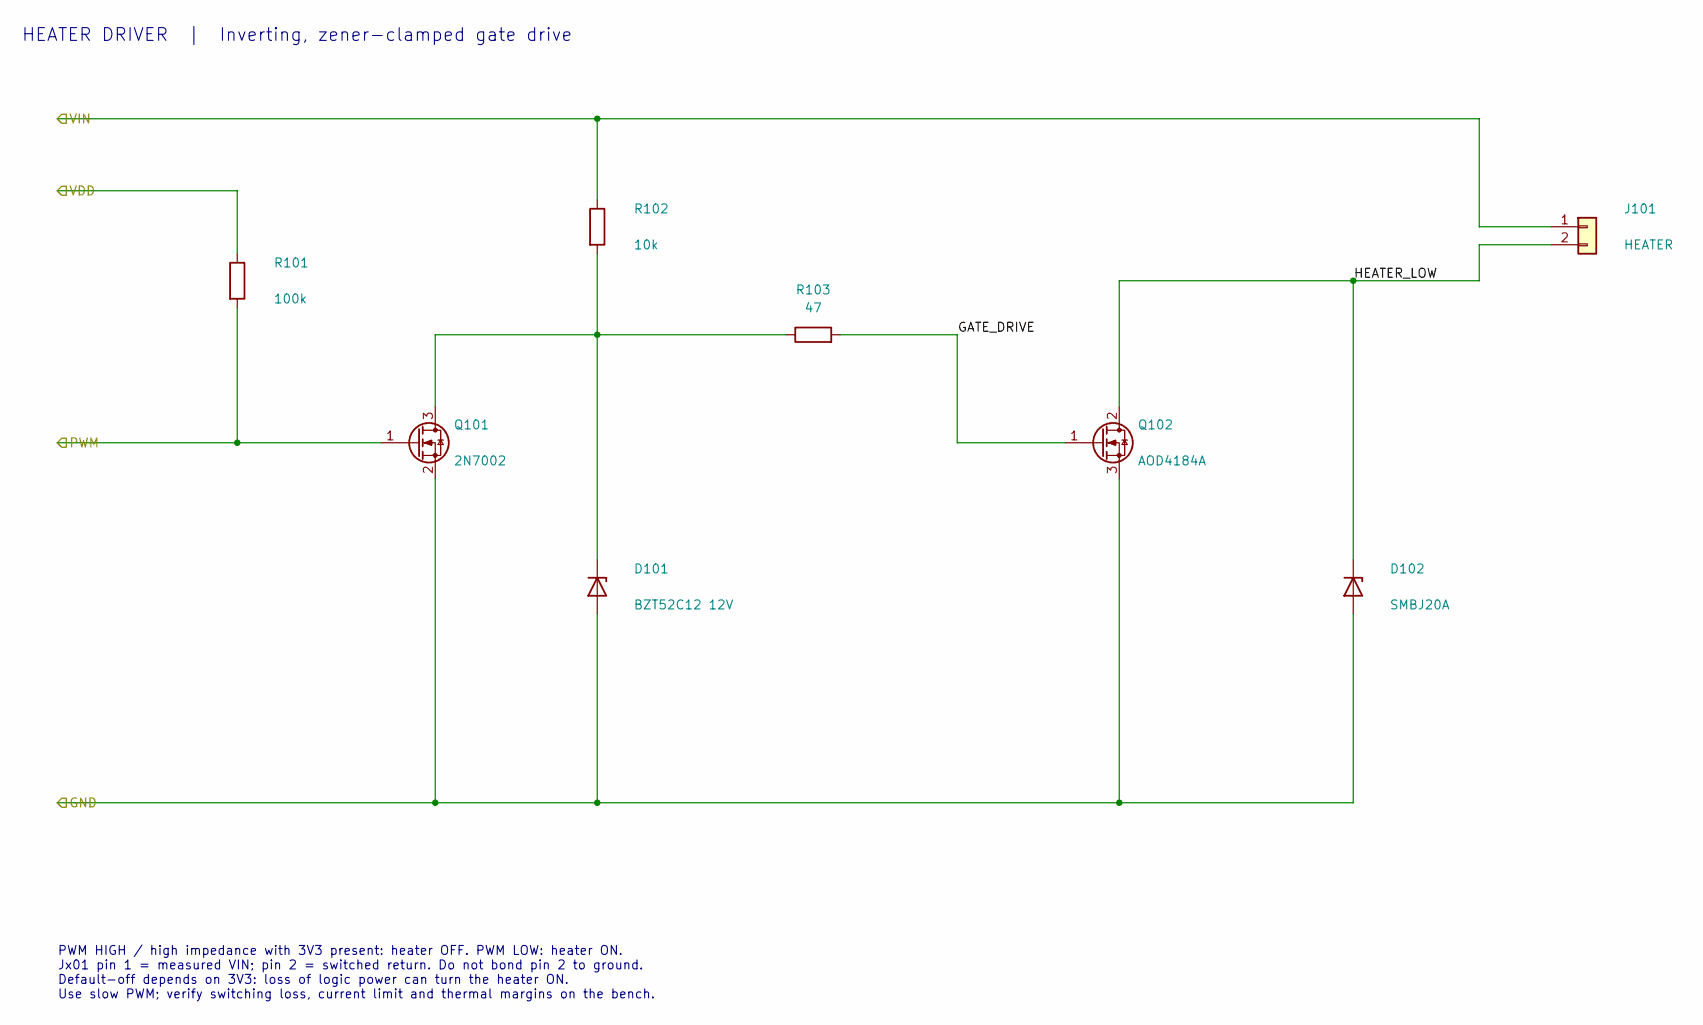
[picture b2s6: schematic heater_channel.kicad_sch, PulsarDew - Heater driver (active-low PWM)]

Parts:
D101: BZT52C12 12V; D_SOD-123; MPN BZT52C12; LCSC C19077410
D102: SMBJ20A; D_SMB_Handsoldering; MPN SMBJ20A; LCSC C364296
J101: HEATER; TerminalBlock_Phoenix_MKDS-1,5-2-5.08_1x02_P5.08mm_Horizont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
Q101: 2N7002; SOT-23; MPN 2N7002; LCSC C8545
Q102: AOD4184A; TO-252-2; MPN AOD4184A; LCSC C5370959
R101: 100k; R_0402_1005Metric
R102: 10k; R_0402_1005Metric
R103: 47; R_0402_1005Metric

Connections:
/+3V3: R101.1; also elsewhere on the board
/GND: D101.2 (A), D102.2 (A), Q101.2 (S), Q102.3 (S); also elsewhere on the board
/HTR_PWM0: Q101.1 (G), R101.2; also elsewhere on the board
/Heater Ch0/GATE_DRIVE: Q102.1 (G), R103.2
/Heater Ch0/HEATER_LOW: D102.1 (K), J101.2, Q102.2 (D)
/VIN_HEAT: J101.1, R102.1; also elsewhere on the board
unnamed: D101.1 (K), Q101.3 (D), R102.2, R103.1

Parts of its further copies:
D201, D301, D401: BZT52C12 12V; D_SOD-123; MPN BZT52C12; LCSC C19077410
D202, D302, D402: SMBJ20A; D_SMB_Handsoldering; MPN SMBJ20A; LCSC C364296
J201, J301, J401: HEATER; TerminalBlock_Phoenix_MKDS-1,5-2-5.08_1x02_P5.08mm_Horizont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
Q201, Q301, Q401: 2N7002; SOT-23; MPN 2N7002; LCSC C8545
Q202, Q302, Q402: AOD4184A; TO-252-2; MPN AOD4184A; LCSC C5370959
R201, R301, R401: 100k; R_0402_1005Metric
R202, R302, R402: 10k; R_0402_1005Metric
R203, R303, R403: 47; R_0402_1005Metric

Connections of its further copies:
/+3V3: R201.1, R301.1, R401.1; also elsewhere on the board
/GND: D201.2 (A), D202.2 (A), D301.2 (A), D302.2 (A), D401.2 (A), D402.2 (A), Q201.2 (S), Q202.3 (S), Q301.2 (S), Q302.3 (S), Q401.2 (S), Q402.3 (S); also elsewhere on the board
/HTR_PWM1: Q201.1 (G), R201.2; also elsewhere on the board
/HTR_PWM2: Q301.1 (G), R301.2; also elsewhere on the board
/HTR_PWM3: Q401.1 (G), R401.2; also elsewhere on the board
/Heater Ch1/GATE_DRIVE: Q202.1 (G), R203.2
/Heater Ch1/HEATER_LOW: D202.1 (K), J201.2, Q202.2 (D)
/Heater Ch2/GATE_DRIVE: Q302.1 (G), R303.2
/Heater Ch2/HEATER_LOW: D302.1 (K), J301.2, Q302.2 (D)
/Heater Ch3/GATE_DRIVE: Q402.1 (G), R403.2
/Heater Ch3/HEATER_LOW: D402.1 (K), J401.2, Q402.2 (D)
/VIN_HEAT: J201.1, J301.1, J401.1, R202.1, R302.1, R402.1; also elsewhere on the board
unnamed: D201.1 (K), Q201.3 (D), R202.2, R203.1
unnamed: D301.1 (K), Q301.3 (D), R302.2, R303.1
unnamed: D401.1 (K), Q401.3 (D), R402.2, R403.1

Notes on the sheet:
HEATER DRIVER | Inverting, zener-clamped gate drive
PWM HIGH / high impedance with 3V3 present: heater OFF. PWM LOW: heater ON. Jx01 pin 1 = measured VIN; pin 2 = switched return. Do not bond pin 2 to ground. Default-off depends on 3V3: loss of logic power can turn the heater ON. Use slow PWM; verify switching loss, current limit and thermal margins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

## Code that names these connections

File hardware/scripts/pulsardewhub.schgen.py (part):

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 named(s,ref,4,'INPUT_GATE')
 s.wire(s.pins[ref]['1'],(s.pins[ref]['1'][0],71.12))
 s.wire(s.pins[ref]['5'],(s.pins[ref]['5'][0],30.48))
s.wire((160.02,71.12),(210.82,71.12));s.label('VIN_RAW',(210.82,71.12))
s.wire((160.02,30.48),(210.82,30.48));s.label('VIN',(210.82,30.48))
put(s,'U10','pulsarfab_hub:LM74700QDBV',139.7,101.6,code='C2941042')
for n,name in [(6,'VIN_RAW'),(3,'VIN_RAW'),(1,'VCAP'),(2,'GND'),(4,'VIN'),(5,'INPUT_GATE')]:named(s,'U10',n,name)
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s=make('controller','STM32 controller and ambient sensor','A3')
s.text('CONTROLLER | 2 heater PWM + 4 DC enables / ADC current readings / faults',20,16,2)
put(s,'U1','pulsarfab:STM32G0B1KBU6',132.08,86.36,fp='Package_DFN_QFN:UFQFPN-32-1EP_5x5mm_P0.5mm_EP3.5x3.5mm',code='C5159549')
gpio={7:'HTR0',8:'HTR1',11:'IMON1',12:'IMON2',13:'IMON3',14:'IMON4',15:'DC_EN1',16:'DC_EN2',17:'DC_EN3',1:'DC_EN4',27:'DC_PG1',28:'DC_PG2',29:'DC_PG3',20:'DC_PG4',22:'MCU_DM',23:'MCU_DP',19:'USB_ATTACH',24:'SWDIO',25:'SWCLK',30:'SCL',31:'SDA',4:'V3',5:'GND',33:'GND',6:'NRST'}
for n,name in gpio.items():named(s,'U1',n,name)
nc_rest(s,'U1',gpio)
for r,x,v in [('C1',68.58,'100n'),('C2',88.9,'4.7u / 16V')]:branch(s,r,'Device:C',x,48.26,v,'V3','GND',code='C14663' if r=='C1' else '')
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 put(s,'J'+str(b),'Connector_Generic:Conn_01x02',x+30.48,48.26,'HEATER '+str(i+1),'pulsarfab:TerminalBlock_KEFA_KF128_2P_P5.08mm','C474952')
 named(s,'J'+str(b),2,f'HEATER{i}_LOW')
 ff=put(s,'F'+str(b),'Device:Fuse',x,48.26,'7A heater fuse','Fuse:Fuse_Littelfuse-NANO2-451_453','C99548',90)
 s.wire(ff['2'],s.pins['J'+str(b)]['1']);named(s,'F'+str(b),1,'HTR_VIN')
 branch(s,'D'+str(b),'Device:D_Zener',x+33.02,99.06,'SMBJ20A',f'HEATER{i}_LOW','GND','Diode_SMD:D_SMB','C364296',angle=270)
put(s,'U51','Sensor_Energy:INA226',119.38,218.44,code='C49851')
put(s,'R50','Device:R',60.96,177.8,'2m / 3W / 1%','Resistor_SMD:R_2512_6332Metric','C2994640',90)
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 p=dcput(ref,'Device:C',x,y,v,fp,code);named(s,ref,1,n1,5.08);named(s,ref,2,n2,5.08);return p
ports(s,[('VIN','input'),('V3','input'),('GND','input'),('ENABLE','input'),('CURRENT','output'),('PGOOD','output')],25.4,38.1)
dcput('U101','pulsarfab_hub:TPS25974LRPW',213.36,83.82,code='C3662931')
mapping={5:'VIN',8:'GND',6:'OUT',1:'EN_SW',2:'OV_SENSE',3:'PGOOD',4:'PG_SENSE',9:'IMON_RAW',7:'DVDT'}
for n,name in mapping.items():named(s,'U101',n,name)
nc_rest(s,'U101',mapping) # ITIMER open: fastest overload response. L variant: latch-off.
dcr('R101',83.82,139.7,'100k','OUT','PG_SENSE');dcr('R102',83.82,185.42,'20k','PG_SENSE','GND')
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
